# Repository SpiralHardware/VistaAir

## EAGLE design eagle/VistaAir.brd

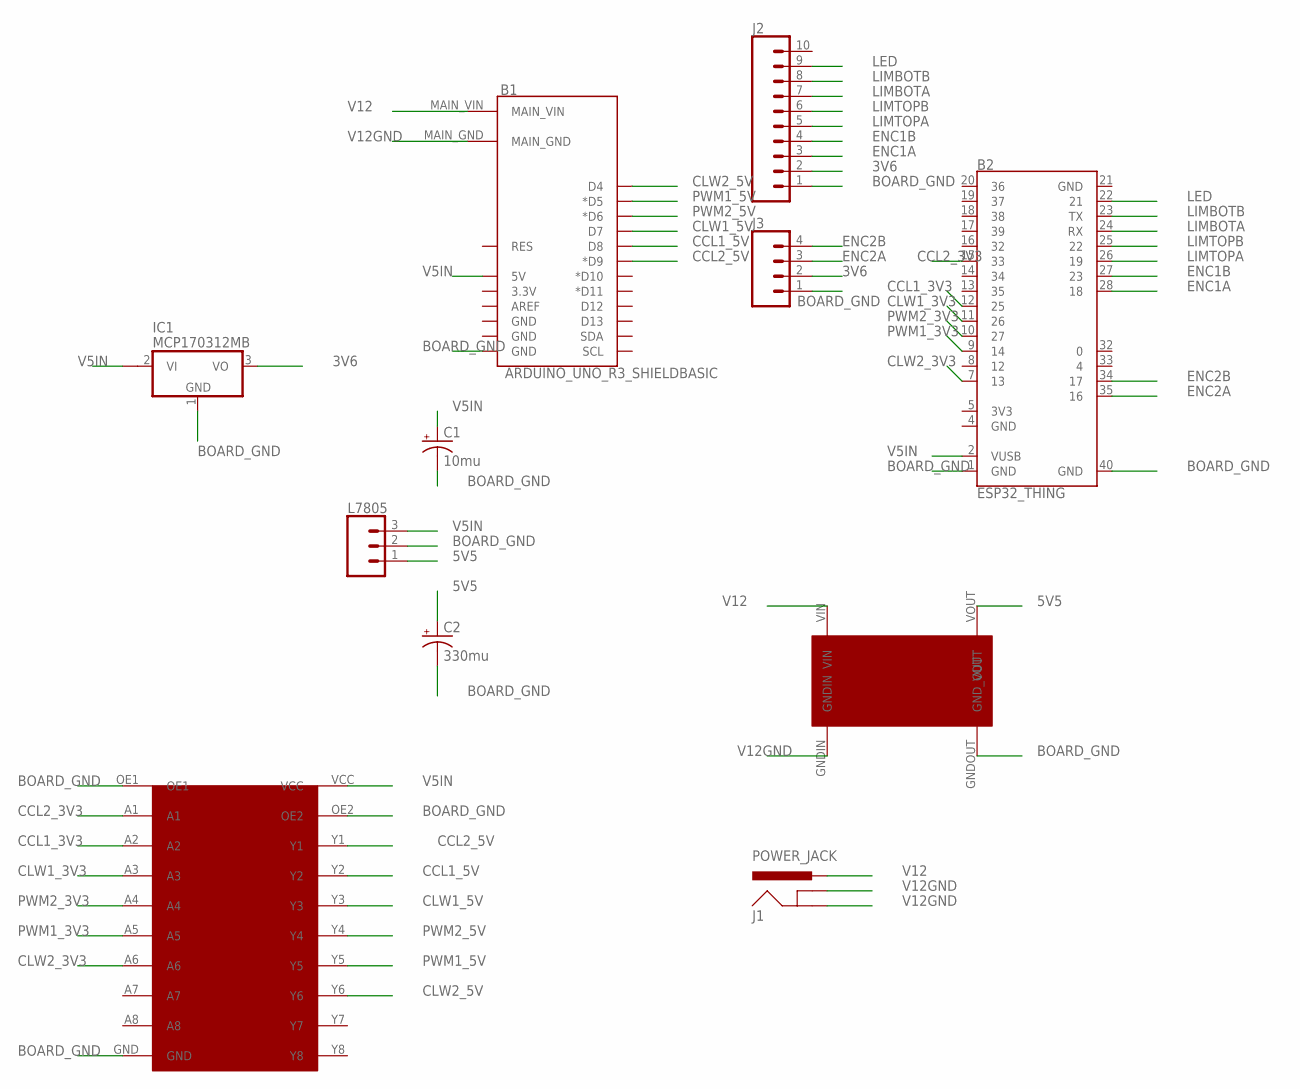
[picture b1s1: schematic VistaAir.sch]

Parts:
B1: ARDUINO_UNO_R3_SHIELDBASIC; UNO_R3_SHIELD
B2: ESP32_THING
C1: 10mu; TT2D5
C2: 330mu; TT5D10
IC1: MCP170312MB; SOT89
J1: POWER_JACK; POWER_JACK_PTH
J2: CONN_10"; 1X10
J3: CONN_04; 1X04
L7805: CONN_03; 1X03
U$1: SN74AHCT541_SOIC-20; SN74AHCT541
U$2: LM2596_STEPDOWN_MODULE

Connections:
3V6: IC1.3 (VO), J2.2, J3.2
5V5: C2.+, L7805.1, U$2.VOUT
BOARD_GND: B1.BOARD_GND (GND), B2.1 (GND), B2.40 (GND), C1.-, C2.-, IC1.1 (GND), J2.1, J3.1, L7805.2, U$1.GND, U$1.OE1, U$1.OE2, U$2.GNDOUT (GND_OUT)
CCL1_3V3: B2.12 (25), U$1.A2
CCL1_5V: B1.D8, U$1.Y2
CCL2_3V3: B2.15 (33), U$1.A1
CCL2_5V: B1.D9 (*D9), U$1.Y1
CLW1_3V3: B2.11 (26), U$1.A3
CLW1_5V: B1.D7, U$1.Y3
CLW2_3V3: B2.7 (13), U$1.A6
CLW2_5V: B1.D4, U$1.Y6
ENC1A: B2.28 (18), J2.3
ENC1B: B2.27 (23), J2.4
ENC2A: B2.35 (16), J3.3
ENC2B: B2.34 (17), J3.4
LED: B2.22 (21), J2.9
LIMBOTA: B2.24 (RX), J2.7
LIMBOTB: B2.23 (TX), J2.8
LIMTOPA: B2.26 (19), J2.5
LIMTOPB: B2.25 (22), J2.6
PWM1_3V3: B2.9 (14), U$1.A5
PWM1_5V: B1.D5 (*D5), U$1.Y5
PWM2_3V3: B2.10 (27), U$1.A4
PWM2_5V: B1.D6 (*D6), U$1.Y4
V5IN: B1.5V, B2.2 (VUSB), C1.+, IC1.2@1 (VI1), L7805.3, U$1.VCC
V12: B1.MAIN_VIN, J1.PWR, U$2.VIN
V12GND: B1.MAIN_GND, J1.GND, J1.GNDBREAK, U$2.GNDIN

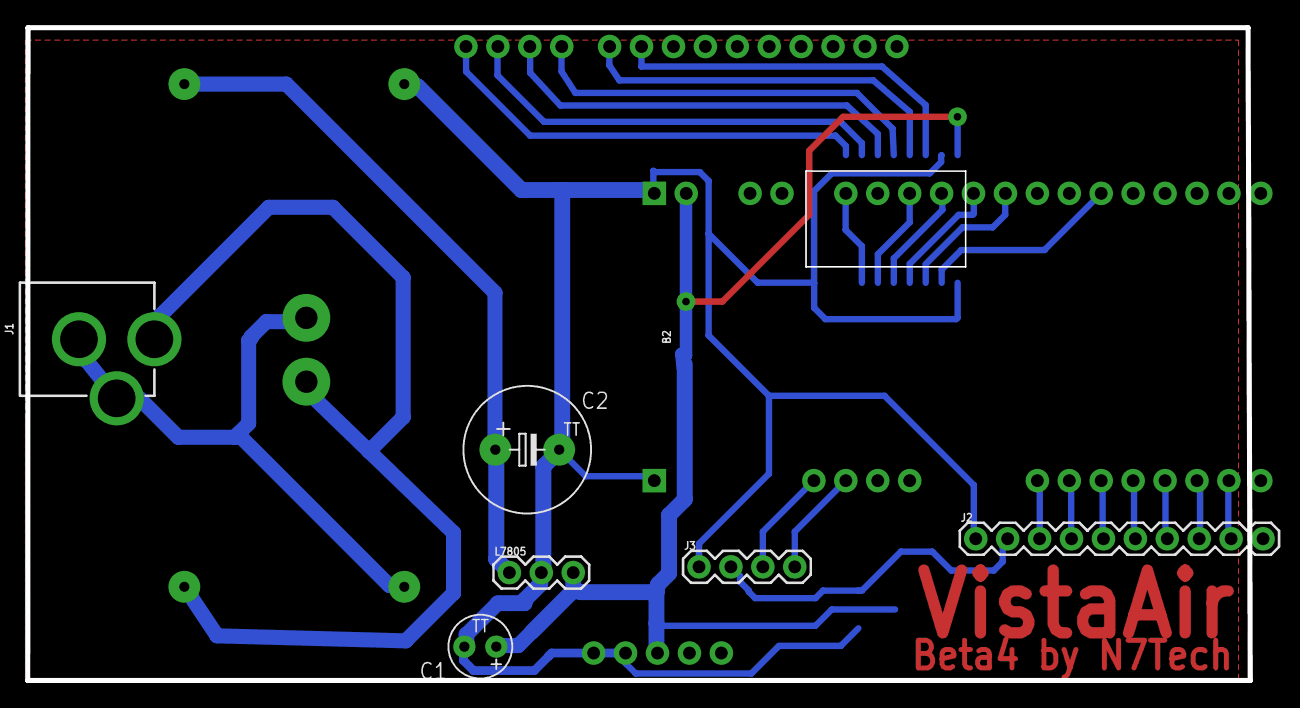
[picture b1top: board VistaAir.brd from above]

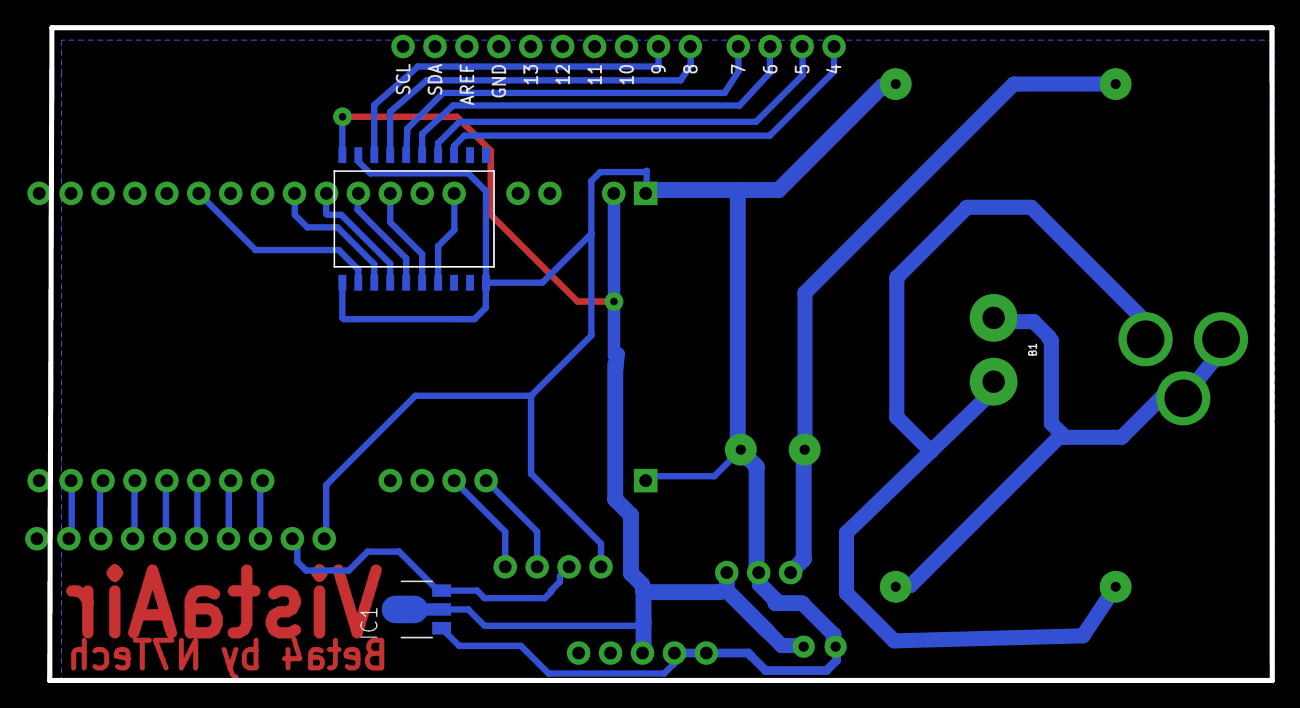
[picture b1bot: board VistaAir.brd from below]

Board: 2 copper layers, 97.3 x 51.9 mm, 11 parts (3 on the bottom side), 27 nets.

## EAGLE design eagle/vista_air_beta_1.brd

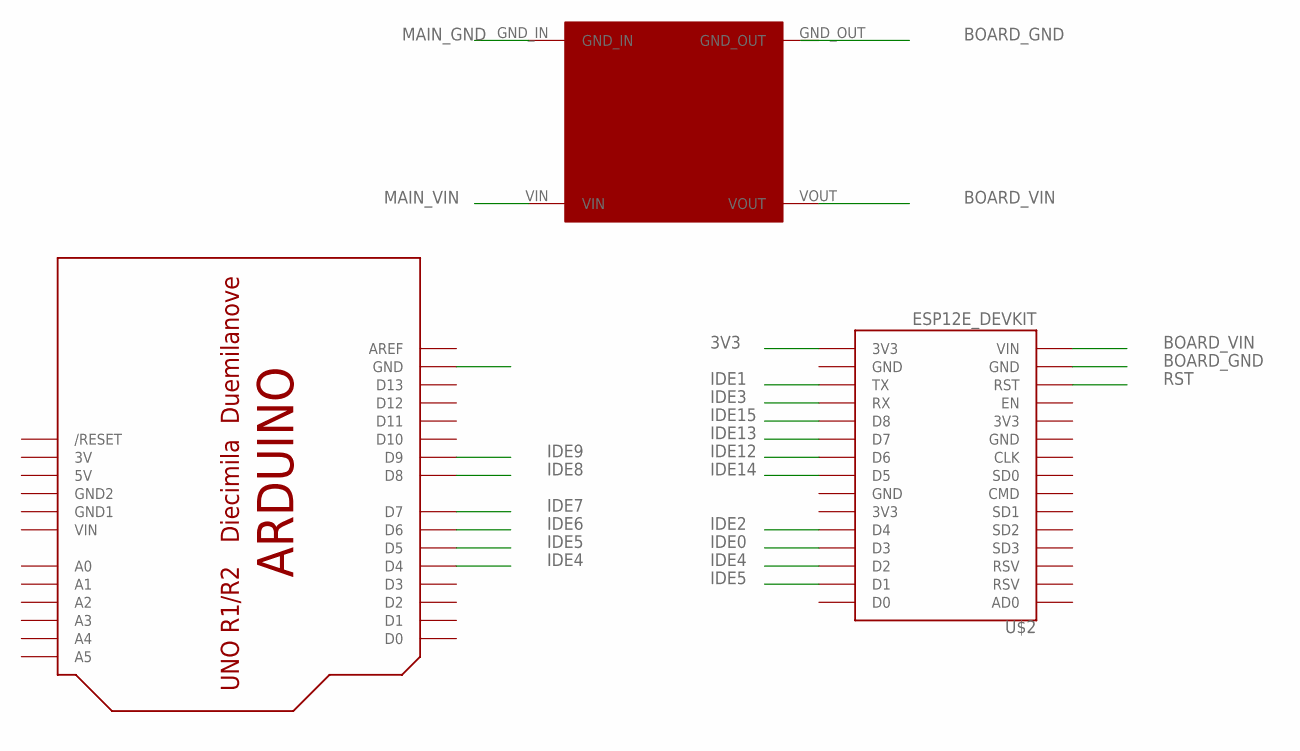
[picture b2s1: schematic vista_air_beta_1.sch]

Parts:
U$1: ARDUINOUNO; ARDUINO
U$2: ESP12E_DEVKIT
U$3: MP1584EN_STEPDOWN_MODULE

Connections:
3V: U$1.3V
3V3: U$2.3V3@2 (3V3)
5V: U$1.5V
BOARD_GND: U$1.GND, U$2.GND@1 (GND)
BOARD_VIN: U$2.VIN, U$3.VOUT
GND1: U$1.GND1
GND2: U$1.GND2
IDE0: U$2.D3
IDE1: U$2.TX
IDE2: U$2.D4
IDE3: U$2.RX
IDE4: U$1.D4, U$2.D2
IDE5: U$1.D5, U$2.D1
IDE6: U$1.D6
IDE7: U$1.D7
IDE8: U$1.D8
IDE9: U$1.D9
IDE12: U$2.D6
IDE13: U$2.D7
IDE14: U$2.D5
IDE15: U$2.D8
MAIN_GND: U$3.GND_IN
MAIN_VIN: U$3.VIN
RST: U$2.RST
VIN: U$1.VIN

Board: 2 copper layers, 3 parts (0 on the bottom side), 4 nets, no tracks yet.

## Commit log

2017-01-23 initial import
2017-01-23 initial import 2
2017-01-23 remove eagle trash
2017-01-23 ignores
2017-01-23 android alpha projects
2017-01-23 up to date eagle files
2017-01-23 pcb corrections
2017-01-23 beta 1 board corrections
2017-01-25 updated board for stable power - which I believe was showstopper
2017-01-26 proper stable power supply on board with buck converter into liner regulators
2017-01-28 update board with logic converer from 3.3v esp32 to 5v monster moto board
2017-01-28 fix missing ground connection to 3.6v regulator
2017-01-28 fix manual routing short
2017-01-29 managed to break ground connection to 3.6v regulator again - fixed it
2017-01-31 board tidy up, encoders working with modified library
2017-02-01 board now with working logic converter
2017-02-07 still trying to get single power board to work with logic shifter - still failing
2017-02-09 barrel jack for board, fix pin numbers for arduino motor test and simplify board - diodes seem to be surplus to requirements. Logic shifting issue is something else
2017-02-11 using one way logic translator since motor driver PWM inputs are open drain - and sets up ultra-high-frequency push pull with bi-directional logic shifter
2017-02-12 first script to test ESP32 motor synch with encoders
2017-02-14 full wifi synched motors beta4 proof of concept - rough edges, but it works
2017-02-28 pin 34 to 35
2017-02-28 Change Port Number to 61

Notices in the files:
parts and their libraries:
SparkFun-Connectors: Licensing: Creative Commons ShareAlike 4.0 International - https://creativecommons.org/licenses/by-sa/4.0
